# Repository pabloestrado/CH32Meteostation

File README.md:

# CH32 Meteostation

This project is a meteostation using the CH32V003A4M6 microcontroller. It includes functionalities for measuring temperature, humidity, and pressure, and displays the data on an SSD1306 OLED screen. The project also supports Bluetooth communication for remote data access.

## Features

- Temperature and humidity measurement using AHT20 sensor
- Pressure measurement using BMP280 sensor
- Display data on SSD1306 OLED screen
- Bluetooth communication using JDY-23 module
- Battery voltage monitoring
- Deep sleep mode for power saving

## Hardware Requirements

- CH32 microcontroller
- AHT20 temperature and humidity sensor
- BMP280 pressure sensor
- SSD1306 OLED display
- JDY-23 Bluetooth module
- Battery and power management components

## Software Requirements

- PlatformIO
- CH32V003 SDK
- I2C, UART, and GPIO libraries

## Setup

1. Clone the repository:
    ```sh
    git clone https://github.com/yourusername/CH32Meteostation.git
    cd CH32Meteostation
    ```

2. Open the project in PlatformIO:
    ```sh
    platformio init --board ch32v003
    ```

3. Build and upload the firmware:
    ```sh
    platformio run --target upload
    ```

## Usage

1. Power on the device.
2. The device will initialize and start measuring the environmental data.
3. The data will be displayed on the OLED screen.
4. Use a Bluetooth-enabled device to connect and retrieve data remotely.

## Code Overview

- `main.c`: The main application code, including initialization, measurement, display, and communication functions.
- `i2c.c` and `i2c.h`: I2C communication functions.
- `uart.c` and `uart.h`: UART communication functions.
- `ssd1306.c` and `ssd1306.h`: SSD1306 OLED display functions.
- `bmp280.c` and `bmp280.h`: BMP280 sensor functions.
- `aht20.c` and `aht20.h`: AHT20 sensor functions.

## License

This project is licensed under the MIT License. See the [LICENSE](LICENSE) file for details.

## Acknowledgements

- [PlatformIO](https://platformio.org/)
- [ch32fun](https://github.com/cnlohr/ch32fun)

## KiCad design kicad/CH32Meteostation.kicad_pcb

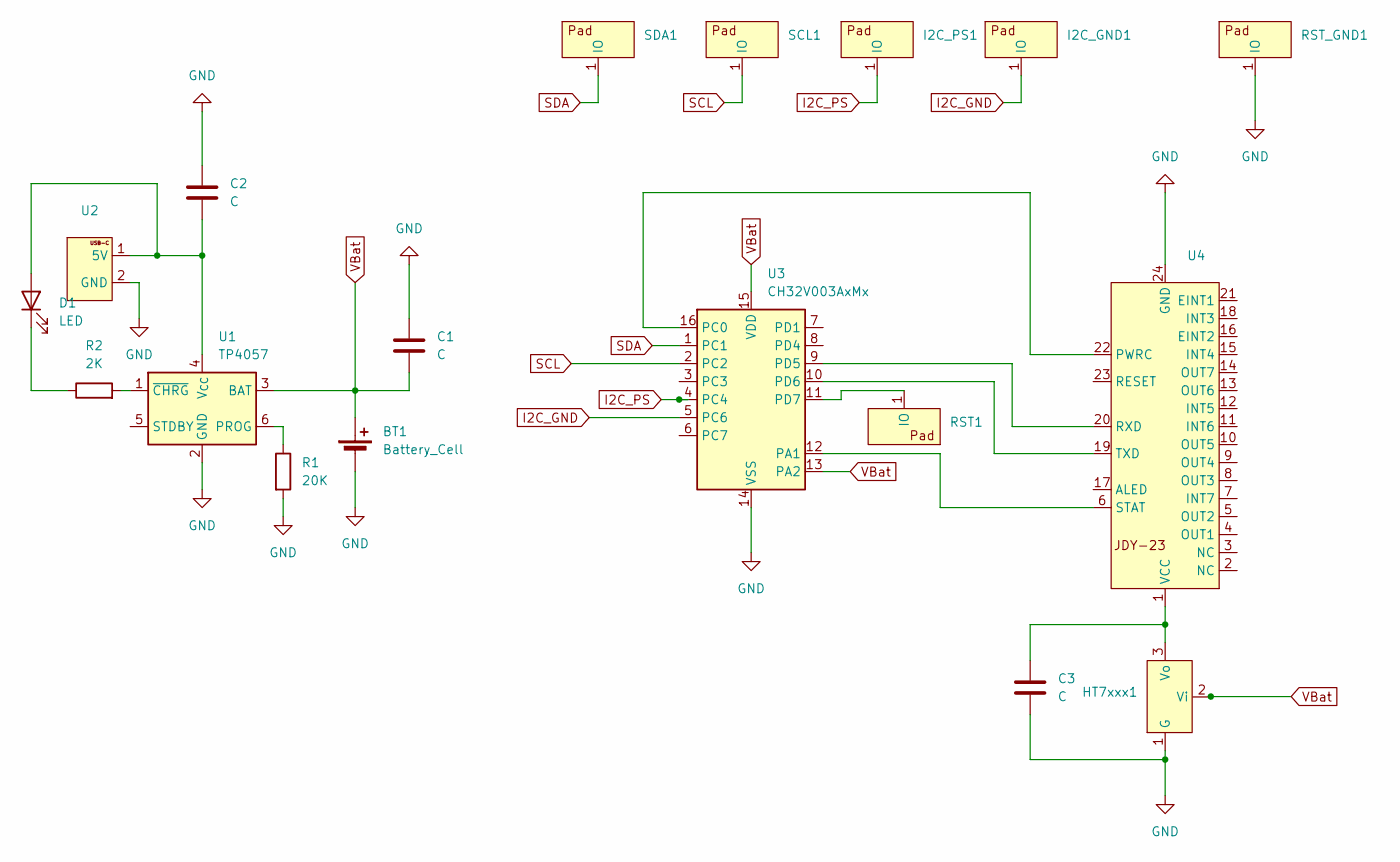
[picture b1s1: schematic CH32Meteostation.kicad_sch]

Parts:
BT1: Battery_Cell; 2-pin soldering pad
C1, C2, C3: C; C_1206_3216Metric_Pad1.33x1.80mm_HandSolder
D1: LED; DIP2 device
HT7xxx1: SOT-89-3_Handsoldering
I2C_GND1, I2C_PS1: Soldering pad
R1: 20K; R_1206_3216Metric_Pad1.30x1.75mm_HandSolder
R2: 2K; R_1206_3216Metric_Pad1.30x1.75mm_HandSolder
RST1: Soldering pad
RST_GND1: Soldering pad
SCL1: Soldering pad
SDA1: Soldering pad
U1: TP4057; TSOT-23-6
U2: USB_C_2pin-poweronly
U3: CH32V003AxMx; SOP-16_3.9x9.9mm_P1.27mm
U4: JDY-23

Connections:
GND: BT1.2 (-), C1.1, C2.1, C3.2, HT7xxx1.1 (G), R1.2, RST_GND1.1 (IO), U1.2 (GND), U2.2 (GND), U3.14 (VSS), U4.24 (GND)
I2C_GND: I2C_GND1.1 (IO), U3.5 (PC6)
I2C_PS: I2C_PS1.1 (IO), U3.4 (PC4)
unnamed: C2.2, D1.2 (A), U1.4 (V_{CC}), U2.1 (5V)
unnamed: D1.1 (K), R2.1
unnamed: C3.1, HT7xxx1.3 (Vo), U4.1 (VCC)
unnamed: RST1.1 (IO), U3.11 (PD7)
unnamed: R1.1, U1.6 (PROG)
unnamed: R2.2, U1.1 (~CHRG)
unnamed: U3.12 (PA1), U4.6 (STAT)
unnamed: U3.16 (PC0), U4.22 (PWRC)
unnamed: U3.9 (PD5), U4.20 (RXD)
unnamed: U3.10 (PD6), U4.19 (TXD)
SCL: SCL1.1 (IO), U3.2 (PC2)
SDA: SDA1.1 (IO), U3.1 (PC1)
VBat: BT1.1 (+), C1.2, HT7xxx1.2 (Vi), U1.3 (BAT), U3.13 (PA2), U3.15 (VDD)

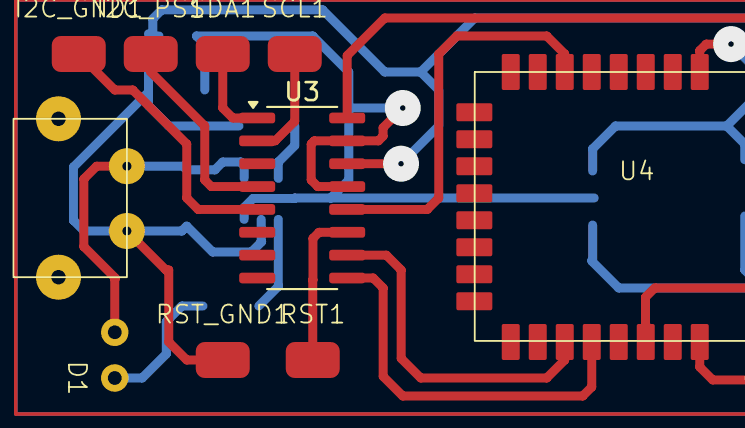
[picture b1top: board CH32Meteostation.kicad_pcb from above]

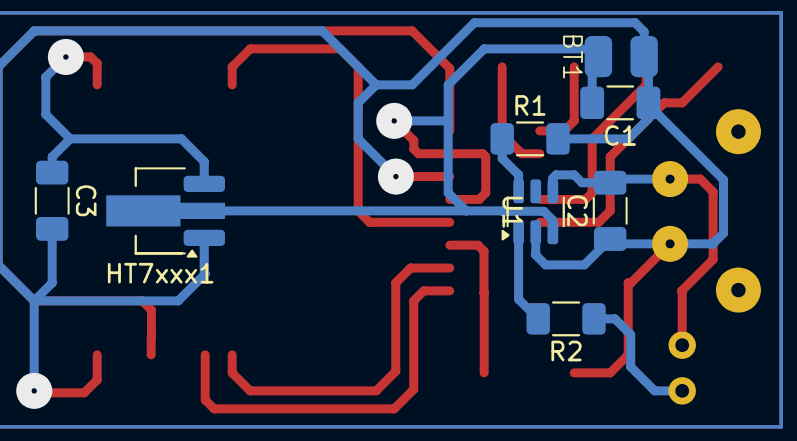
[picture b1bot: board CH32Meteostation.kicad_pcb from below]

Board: 2 copper layers, 18 parts (8 on the bottom side), 16 nets.

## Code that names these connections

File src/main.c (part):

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
#define WD_TIMEOUT_MS 15000 // Reset if stuck for more that 15s

#define I2C_GND_PIN PC6
#define I2C_VCC_PIN PC4
#define WAKEUP_PIN PA1
#define BAT_ADC_PIN ANALOG_0
#define JDY23_PWRC_PIN PC0

// Preshared key for BLE auth
#define AUTH_PSK "123"
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				   (GPIO_CNF_IN_PUPD<<(4*0));


	funPinMode(I2C_GND_PIN, GPIO_Speed_2MHz | GPIO_CNF_OUT_OD);
	funPinMode(I2C_VCC_PIN, GPIO_Speed_2MHz | GPIO_CNF_OUT_PP);
	funPinMode(WAKEUP_PIN, GPIO_CFGLR_IN_PUPD);
	funPinMode(JDY23_PWRC_PIN, GPIO_Speed_2MHz | GPIO_CNF_OUT_OD);
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
	// ADC config
	funAnalogInit();
	funPinMode(PA2, GPIO_CNF_IN_ANALOG);

	// PA1 interupt wakeup
	AFIO->EXTICR |= AFIO_EXTICR_EXTI1_PA;
	EXTI->INTENR |= EXTI_INTENR_MR1; // Enable EXT1
	EXTI->RTENR |= EXTI_RTENR_TR1;
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	uart_print("+MCUREADY\r\n");

	// Sink power for screen and sensor GND
	funDigitalWrite(I2C_GND_PIN, 0);

	Delay_Ms(50);

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	uart_deinit();

    //Disable and reset ADC
	funPinMode(PA2, GPIO_CNF_OUT_PP);
    RCC->APB2PCENR &= ~RCC_APB2Periph_ADC1;
    RCC->APB2PRSTR |= RCC_APB2Periph_ADC1;

	funDigitalWrite(I2C_VCC_PIN, 0);
	funPinMode(I2C_VCC_PIN, GPIO_CNF_OUT_OD);
	funPinMode(I2C_GND_PIN, GPIO_CNF_OUT_OD);

	//power off SCL
	// funPinMode(PC1, GPIO_CNF_OUT_OD);
	// funPinMode(PC1, GPIO_CNF_OUT_OD);
	funPinMode(PD1, GPIO_CNF_IN_PUPD); // disable floating in SWIO pin for power eficiency
	
	//funPinMode(JDY23_PWRC_PIN, GPIO_CNF_IN_PUPD);
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	ssd1306_setbuf(0);
	ssd1306_refresh();
	
	funDigitalWrite(I2C_GND_PIN, 1);

	deepsleep();

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
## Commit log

2025-02-02 sensors working
2025-02-03 Refactored
2025-03-06 Add readme
2025-03-06 Add KiCad files
2025-03-06 Add .vscode
2025-03-06 test
